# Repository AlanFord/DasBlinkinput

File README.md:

# DasBlinkinput
DasBlinkinput for Contextual Electronics course

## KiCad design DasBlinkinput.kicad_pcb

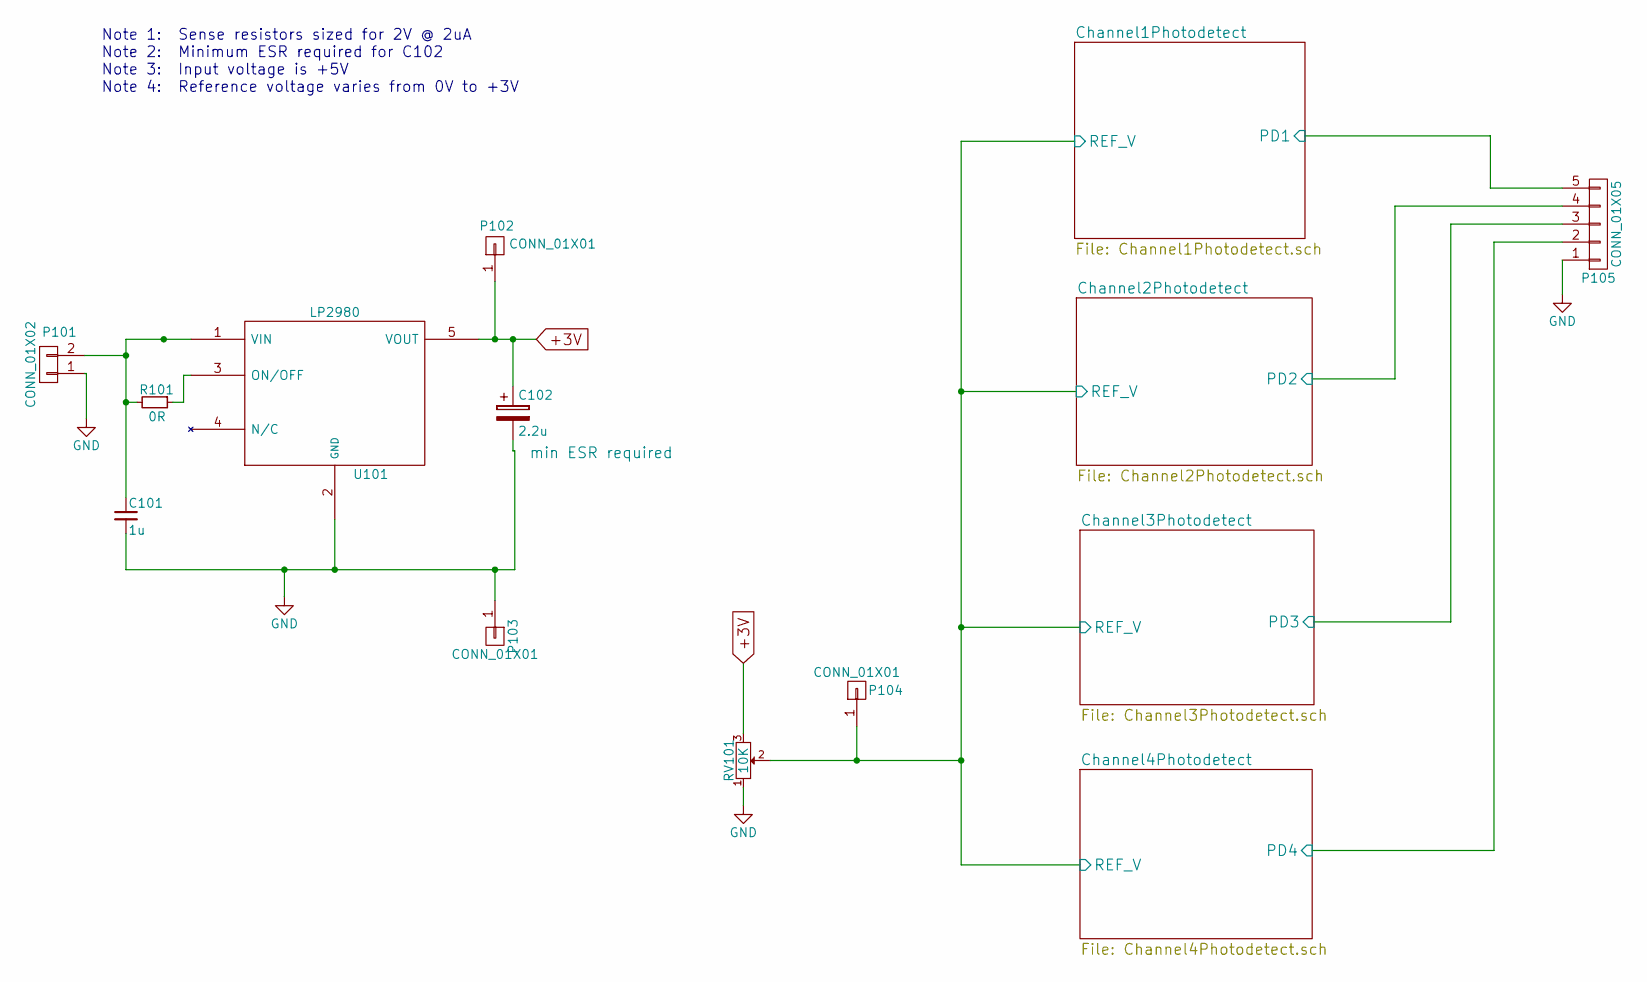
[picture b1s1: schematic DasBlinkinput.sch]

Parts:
C101: 1u; C_0805_HandSoldering
C102: 2.2u; TantalC_SizeA_EIA-3216_HandSoldering; MPN 293D225X0010A2TE3
P101: CONN_01X02; Pin_Header_Straight_1x02
P102, P103, P104: CONN_01X01; Pin_Header_Straight_1x01
P105: CONN_01X05; Pin_Header_Straight_1x05
R101: 0R; R_0805_HandSoldering
RV101: 10K; EVM-3YSX50B14; MPN EVM-3YSX50B14
U101: LP2980; SOT-23-5; MPN LP2980IM5-3.0

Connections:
+3V: C102.1, P102.1, RV101.3, U101.5 (VOUT); also elsewhere on the board
/Channel1Photodetect/PD1: P105.5; also elsewhere on the board
/Channel1Photodetect/REF_V: P104.1, RV101.2; also elsewhere on the board
/Channel2Photodetect/PD2: P105.4; also elsewhere on the board
/Channel3Photodetect/PD3: P105.3; also elsewhere on the board
/Channel4Photodetect/PD4: P105.2; also elsewhere on the board
GND: C101.2, C102.2, P101.1, P103.1, P105.1, RV101.1, U101.2 (GND); also elsewhere on the board
unnamed: C101.1, P101.2, R101.2, U101.1 (VIN)
unnamed: R101.1, U101.3 (ON/OFF)

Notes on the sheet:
Note 1: Sense resistors sized for 2V @ 2uA Note 2: Minimum ESR required for C102 Note 3: Input voltage is +5V Note 4: Reference voltage varies from 0V to +3V

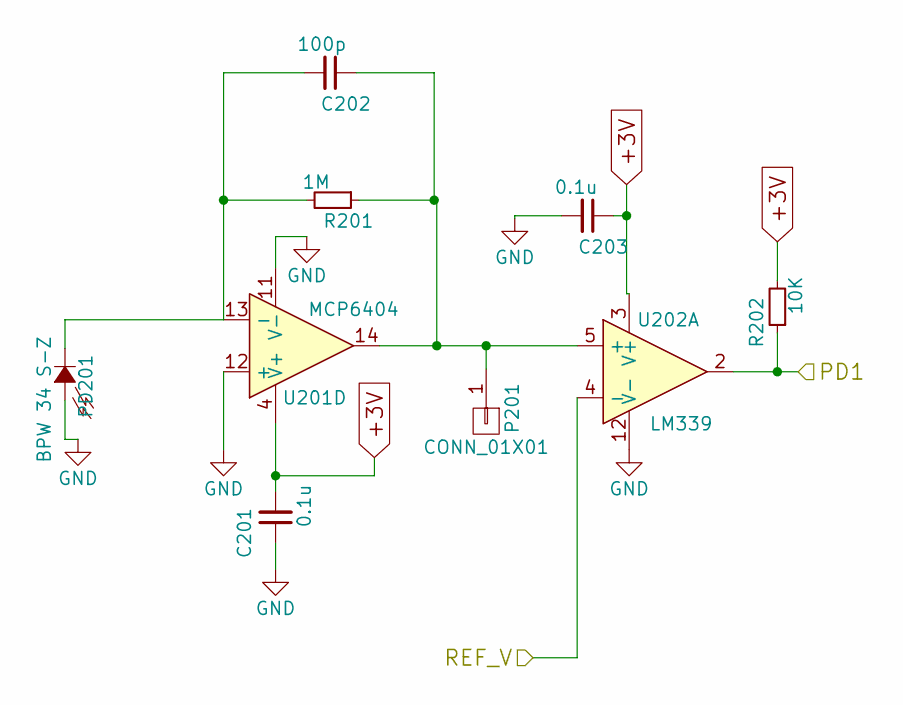
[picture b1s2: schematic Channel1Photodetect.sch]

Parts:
C201, C203: 0.1u; C_0805_HandSoldering
C202: 100p; C_0805_HandSoldering
P201: CONN_01X01; Pin_Header_Straight_1x01
PD201: BPW 34 S-Z; VBPW34S
R201: 1M; R_0805_HandSoldering
R202: 10K; R_0805_HandSoldering
U201: MCP6404; SOIC-14_3.9x8.7mm_Pitch1.27mm; MPN MCP6404-E/SL
U202: LM339; SOIC-14_3.9x8.7mm_Pitch1.27mm; MPN LM339DE4

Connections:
+3V: C201.2, C203.1, R202.2, U201.4 (V+), U202.3 (V+); also elsewhere on the board
/Channel1Photodetect/PD1: R202.1, U202.2; also elsewhere on the board
/Channel1Photodetect/REF_V: U202.4 (-); also elsewhere on the board
GND: C201.1, C203.2, PD201.2 (A), U201.11 (V-), U201.12 (+), U202.12 (V-); also elsewhere on the board
unnamed: C202.1, P201.1, R201.1, U201.14, U202.5 (+)
unnamed: C202.2, PD201.1 (K), R201.2, U201.13 (-)

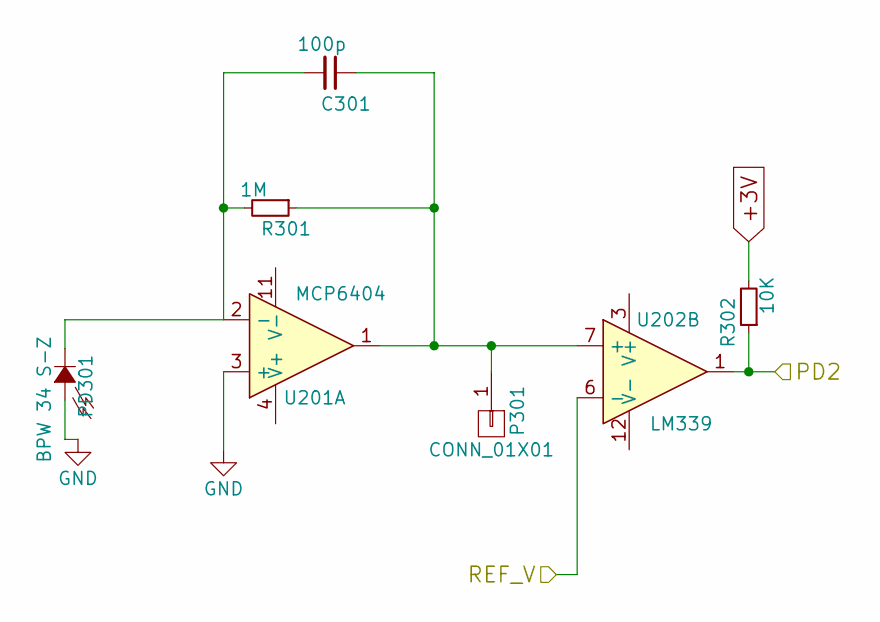
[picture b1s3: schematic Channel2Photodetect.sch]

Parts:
C301: 100p; C_0805_HandSoldering
P301: CONN_01X01; Pin_Header_Straight_1x01
PD301: BPW 34 S-Z; VBPW34S
R301: 1M; R_0805_HandSoldering
R302: 10K; R_0805_HandSoldering
U201: MCP6404; SOIC-14_3.9x8.7mm_Pitch1.27mm
U202: LM339; SOIC-14_3.9x8.7mm_Pitch1.27mm; MPN LM339DE4

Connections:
+3V: R302.2, U201.4 (V+), U202.3 (V+); also elsewhere on the board
/Channel1Photodetect/REF_V: U202.6 (-); also elsewhere on the board
/Channel2Photodetect/PD2: R302.1, U202.1; also elsewhere on the board
GND: PD301.2 (A), U201.3 (+), U201.11 (V-), U202.12 (V-); also elsewhere on the board
unnamed: C301.1, P301.1, R301.1, U201.1, U202.7 (+)
unnamed: C301.2, PD301.1 (K), R301.2, U201.2 (-)

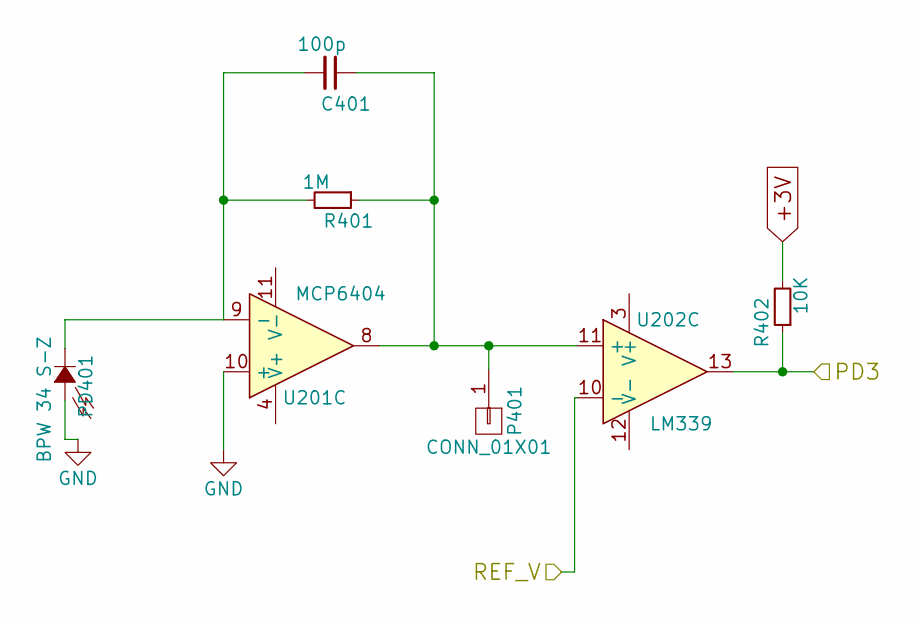
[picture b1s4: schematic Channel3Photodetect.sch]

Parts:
C401: 100p; C_0805_HandSoldering
P401: CONN_01X01; Pin_Header_Straight_1x01
PD401: BPW 34 S-Z; VBPW34S
R401: 1M; R_0805_HandSoldering
R402: 10K; R_0805_HandSoldering
U201: MCP6404; SOIC-14_3.9x8.7mm_Pitch1.27mm
U202: LM339; SOIC-14_3.9x8.7mm_Pitch1.27mm; MPN LM339DE4

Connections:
+3V: R402.2, U201.4 (V+), U202.3 (V+); also elsewhere on the board
/Channel1Photodetect/REF_V: U202.10 (-); also elsewhere on the board
/Channel3Photodetect/PD3: R402.1, U202.13; also elsewhere on the board
GND: PD401.2 (A), U201.10 (+), U201.11 (V-), U202.12 (V-); also elsewhere on the board
unnamed: C401.1, P401.1, R401.1, U201.8, U202.11 (+)
unnamed: C401.2, PD401.1 (K), R401.2, U201.9 (-)

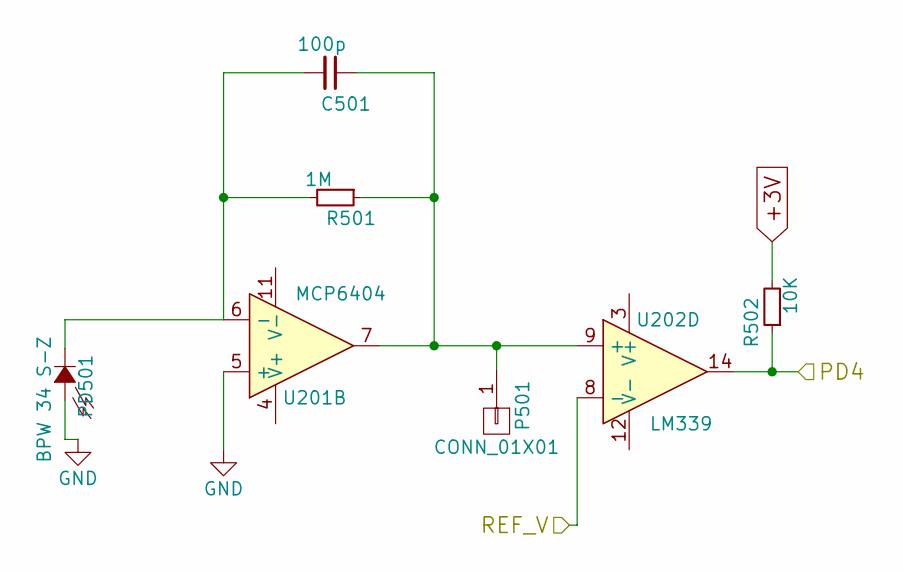
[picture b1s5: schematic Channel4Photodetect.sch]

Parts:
C501: 100p; C_0805_HandSoldering
P501: CONN_01X01; Pin_Header_Straight_1x01
PD501: BPW 34 S-Z; VBPW34S
R501: 1M; R_0805_HandSoldering
R502: 10K; R_0805_HandSoldering
U201: MCP6404; SOIC-14_3.9x8.7mm_Pitch1.27mm
U202: LM339; SOIC-14_3.9x8.7mm_Pitch1.27mm; MPN LM339DE4

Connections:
+3V: R502.2, U201.4 (V+), U202.3 (V+); also elsewhere on the board
/Channel1Photodetect/REF_V: U202.8 (-); also elsewhere on the board
/Channel4Photodetect/PD4: R502.1, U202.14; also elsewhere on the board
GND: PD501.2 (A), U201.5 (+), U201.11 (V-), U202.12 (V-); also elsewhere on the board
unnamed: C501.1, P501.1, R501.1, U201.7, U202.9 (+)
unnamed: C501.2, PD501.1 (K), R501.2, U201.6 (-)

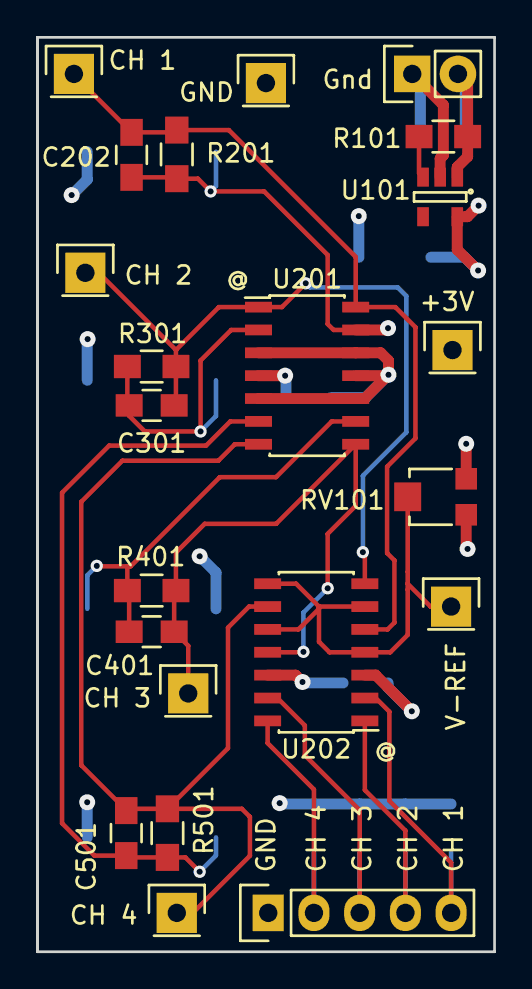
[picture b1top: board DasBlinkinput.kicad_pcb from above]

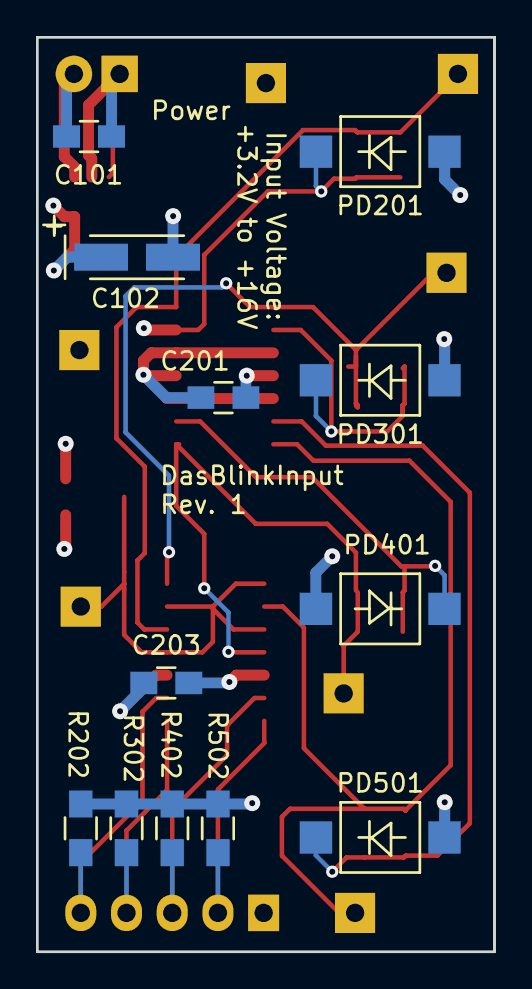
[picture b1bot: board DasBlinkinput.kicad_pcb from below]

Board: 4 copper layers, 25.4 x 50.8 mm, 34 parts (12 on the bottom side), 17 nets.

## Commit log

2016-11-07 LTSpice model initialized
2016-11-10 complete schematic and footprint specification
2016-11-10 revised feedback resistor and updated reference voltage divider
2016-11-14 added pull-up resistors
2016-11-17 expanded and rotated board
2016-11-17 removed 10K resistors used as load for op amps
2016-11-23 replaced potentiometer with trimpot
2016-12-08 completed pcb basic layout
2016-12-15 added labels to silkscreen
2016-12-16 changed photodiodes to BPW 34 S due to availability. Changed feedbak resistor and cap due to increased current output of diode.
2016-12-16 added test points at outputs of op-amps
2016-12-17 modified labels to be indepenent of footprints
2016-12-17 resized labels and added board name and rev
2016-12-18 updated gerbers
2016-12-20 turned off values on gerbers, subtracted soldermask from sikscreen
2016-12-20 udated notes on schematic
2016-12-20 updated gerber files
2016-12-20 repositioned via underneath voltage regulator
2016-12-20 adjust layout of power section
2017-01-22 changed tantalum cap to polarized symbol and tantalum footprint
2017-01-22 corrected inputs on opamp and rerouted traces
2017-01-22 arranged silkscreen labels and generated gerbers
2017-01-22 zipped the gerbers
2017-02-09 LTSpice investigation using Microchip spice model for the op amp
2017-02-09 final revised design
